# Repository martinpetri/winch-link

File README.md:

# winch-link

This is a new project and intended to facilitate communication when launching a paraglider with a winch, as the usual communication via radio often causes problems.

This requires one device for the launch leader and one for the winch.
"winch link" is to transmit the different states like "pilot ready to launch", "pilot hooked in", "tighten rope" etc. to the winch by pressing a button. The winch operator can set his device to confirm automatically or by pressing a button.

Currently the device is under development (See [hardware/winch-link](hardware/winch-link)). The circuit board is drawn and the first prototypes will be ordered in the next weeks. The device will be equipped with an e-paper display so that it can be read in direct sunlight. 

## MIT License

Copyright (c) [2023] [Martin Petri]

Permission is hereby granted, free of charge, to any person obtaining a copy
of this software and associated documentation files (the "Software"), to deal
in the Software without restriction, including without limitation the rights
to use, copy, modify, merge, publish, distribute, sublicense, and/or sell
copies of the Software, and to permit persons to whom the Software is
furnished to do so, subject to the following conditions:

The above copyright notice and this permission notice shall be included in all
copies or substantial portions of the Software.

THE SOFTWARE IS PROVIDED "AS IS", WITHOUT WARRANTY OF ANY KIND, EXPRESS OR
IMPLIED, INCLUDING BUT NOT LIMITED TO THE WARRANTIES OF MERCHANTABILITY,
FITNESS FOR A PARTICULAR PURPOSE AND NONINFRINGEMENT. IN NO EVENT SHALL THE
AUTHORS OR COPYRIGHT HOLDERS BE LIABLE FOR ANY CLAIM, DAMAGES OR OTHER
LIABILITY, WHETHER IN AN ACTION OF CONTRACT, TORT OR OTHERWISE, ARISING FROM,
OUT OF OR IN CONNECTION WITH THE SOFTWARE OR THE USE OR OTHER DEALINGS IN THE
SOFTWARE.

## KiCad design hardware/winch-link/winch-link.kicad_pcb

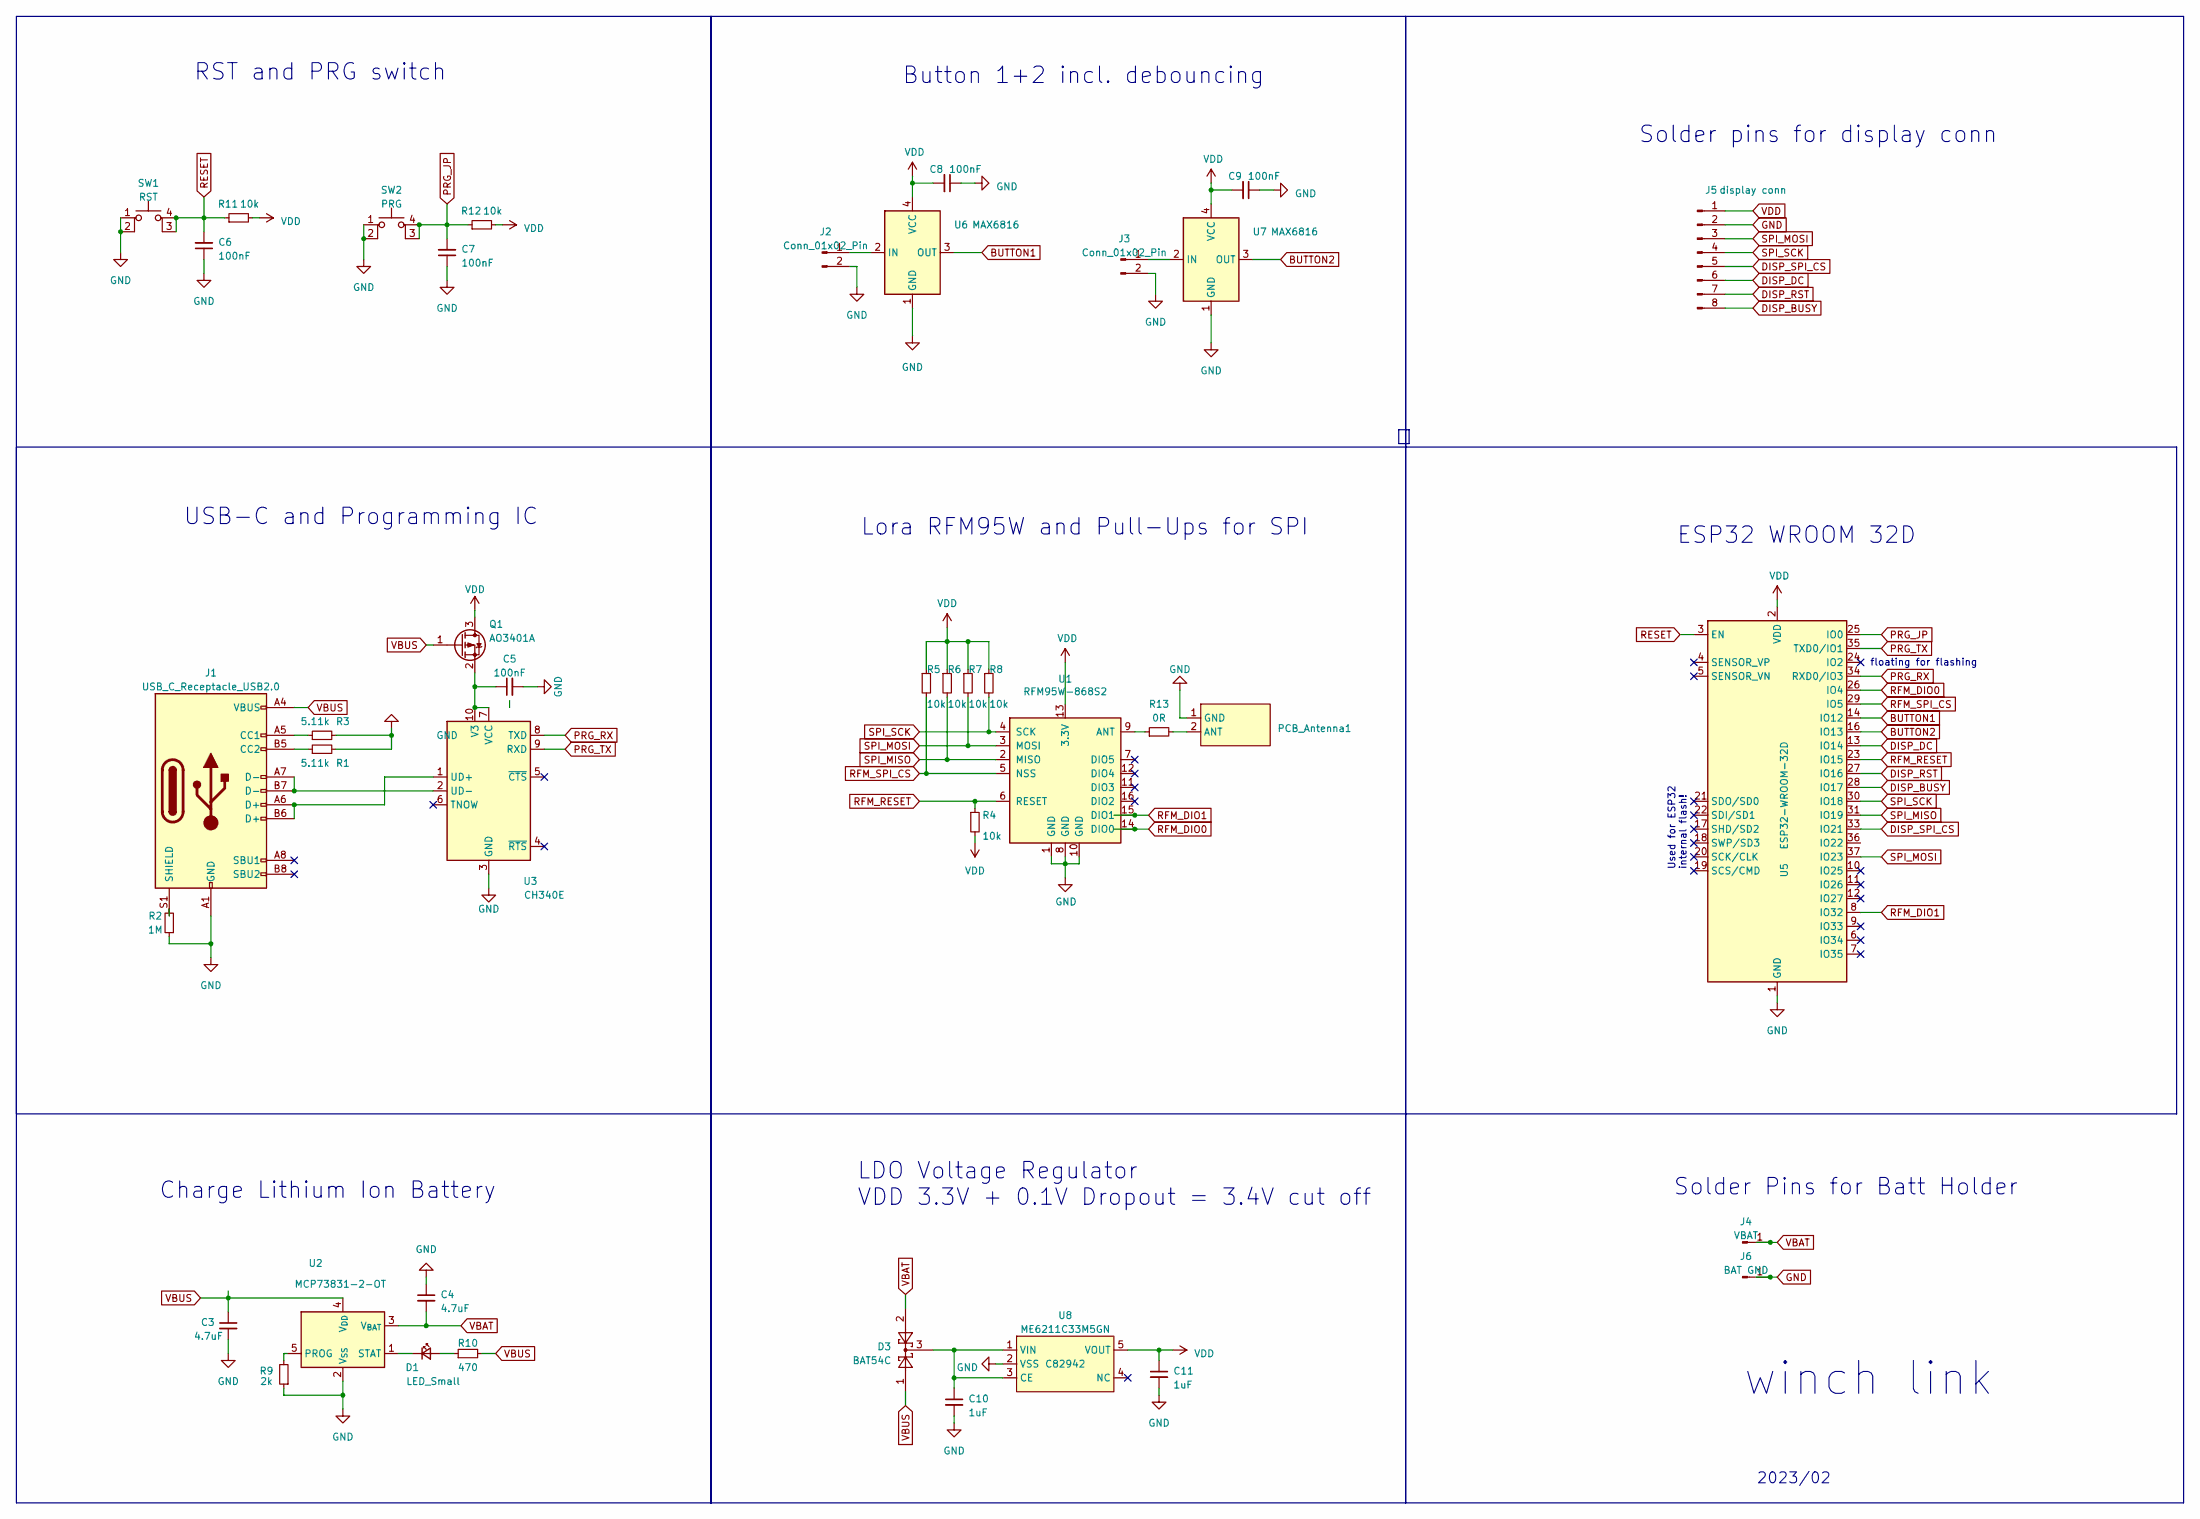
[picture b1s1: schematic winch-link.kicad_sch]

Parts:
C3, C4: 4.7uF; R_0402_1005Metric; LCSC C87147
C5, C6, C7, C8, C9: 100nF; R_0402_1005Metric; LCSC C338032
C10, C11: 1uF; R_0402_1005Metric; LCSC C325464
D1: LED_Small; LED_0603_1608Metric; LCSC C2286
D3: BAT54C; SOT-23; LCSC C171429
J1: USB_C_Receptacle_USB2.0; USB_C_Receptacle_HRO_TYPE-C-31-M-12; LCSC C167321
J2, J3: Conn_01x02_Pin; PinSocket_1x02_P2.54mm_Vertical
J4: VBAT; PinHeader_1x01_P2.54mm_Vertical
J5: display conn; PinHeader_1x08_P2.54mm_Vertical
J6: BAT GND; PinHeader_1x01_P2.54mm_Vertical
PCB_Antenna1: pcb antenna
Q1: AO3401A; SOT-23; LCSC AO3401A
R1, R3: 5.11k; R_0402_1005Metric; LCSC C103084
R2: 1M; R_0402_1005Metric; LCSC C269676
R4, R5, R6, R7, R8, R11, R12: 10k; R_0402_1005Metric; LCSC C406733
R9: 2k; R_0402_1005Metric; LCSC C409711
R10: 470; R_0402_1005Metric; LCSC C114877
R13: 0R; R_0603_1608Metric; LCSC C21189
SW1: RST; SW_TS-1187A-B-A-B; LCSC C318889
SW2: PRG; SW_TS-1187A-B-A-B; LCSC C318889
U1: RFM95W-868S2; HOPERF_RFM9XW_SMD; LCSC C2844472
U2: MCP73831-2-OT; SOT-23-5; LCSC C424093
U3: CH340E; MSOP-10_3x3mm_P0.5mm; LCSC C99652
U5: ESP32-WROOM-32D; LCSC C473012
U6, U7: MAX6816; SOT-143; LCSC C41637
U8: ME6211C33M5GN; SOT-23-5; LCSC C82942

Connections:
BUTTON1: U5.14 (IO12), U6.3 (OUT)
BUTTON2: U5.16 (IO13), U7.3 (OUT)
DISP_BUSY: J5.8, U5.28 (IO17)
DISP_DC: J5.6, U5.13 (IO14)
DISP_RST: J5.7, U5.27 (IO16)
DISP_SPI_CS: J5.5, U5.33 (IO21)
GND: C3.2, C4.1, C5.2, C6.1, C7.1, C8.1, C9.1, C10.2, C11.2, J1.A1 (GND), J1.A12 (GND), J1.B1 (GND), J1.B12 (GND), J2.2, J3.2, J5.2, J6.1, PCB_Antenna1.1 (GND), R1.2, R2.1, R3.2, R9.1, SW1.1, SW1.2, SW2.1, SW2.2, U1.1 (GND), U1.8 (GND), U1.10 (GND), U2.2 (V_{SS}), U3.3 (GND), U5.1 (GND), U5.15 (GND), U5.38 (GND), U5.39 (GND), U6.1 (GND), U7.1 (GND), U8.2 (VSS)
unnamed: D1.2 (A), R10.1
unnamed: D1.1 (K), U2.1 (STAT)
unnamed: J1.A5 (CC1), R3.1
unnamed: J1.B5 (CC2), R1.1
unnamed: J1.S1 (SHIELD), R2.2
unnamed: J2.1, U6.2 (IN)
unnamed: J3.1, U7.2 (IN)
unnamed: PCB_Antenna1.2 (ANT), R13.2
unnamed: C5.1, Q1.2 (S), U3.7 (VCC), U3.10 (V3)
unnamed: R13.1, U1.9 (ANT)
unnamed: R9.2, U2.5 (PROG)
unnamed: J1.A6 (D+), J1.B6 (D+), U3.1 (UD+)
unnamed: J1.A7 (D-), J1.B7 (D-), U3.2 (UD-)
unnamed: C10.1, D3.3, U8.1 (VIN), U8.3 (CE)
PRG_JP: C7.2, R12.1, SW2.3 (K), SW2.4 (A), U5.25 (IO0)
PRG_RX: U3.8 (TXD), U5.34 (RXD0/IO3)
PRG_TX: U3.9 (RXD), U5.35 (TXD0/IO1)
RESET: C6.2, R11.1, SW1.3, SW1.4, U5.3 (EN)
RFM_DIO0: U1.14 (DIO0), U5.26 (IO4)
RFM_DIO1: U1.15 (DIO1), U5.8 (IO32)
RFM_RESET: R4.1, U1.6 (RESET), U5.23 (IO15)
RFM_SPI_CS: R5.2, U1.5 (NSS), U5.29 (IO5)
SPI_MISO: R6.2, U1.2 (MISO), U5.31 (IO19)
SPI_MOSI: J5.3, R7.2, U1.3 (MOSI), U5.37 (IO23)
SPI_SCK: J5.4, R8.2, U1.4 (SCK), U5.30 (IO18)
VBAT: C4.2, D3.2, J4.1, U2.3 (V_{BAT})
VBUS: C3.1, D3.1, J1.A4 (VBUS), J1.A9 (VBUS), J1.B4 (VBUS), J1.B9 (VBUS), Q1.1 (G), R10.2, U2.4 (V_{DD})
VDD: C8.2, C9.2, C11.1, J5.1, Q1.3 (D), R4.2, R5.1, R6.1, R7.1, R8.1, R11.2, R12.2, U1.13 (3.3V), U5.2 (VDD), U6.4 (VCC), U7.4 (VCC), U8.5 (VOUT)

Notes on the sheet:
Lora RFM95W and Pull-Ups for SPI
2023/02
Charge Lithium Ion Battery
floating for flashing
Used for ESP32 internal flash!
Solder Pins for Batt Holder
RST and PRG switch
Solder pins for display conn
LDO Voltage Regulator VDD 3.3V + 0.1V Dropout = 3.4V cut off
ESP32 WROOM 32D
USB-C and Programming IC
Button 1+2 incl. debouncing
winch link

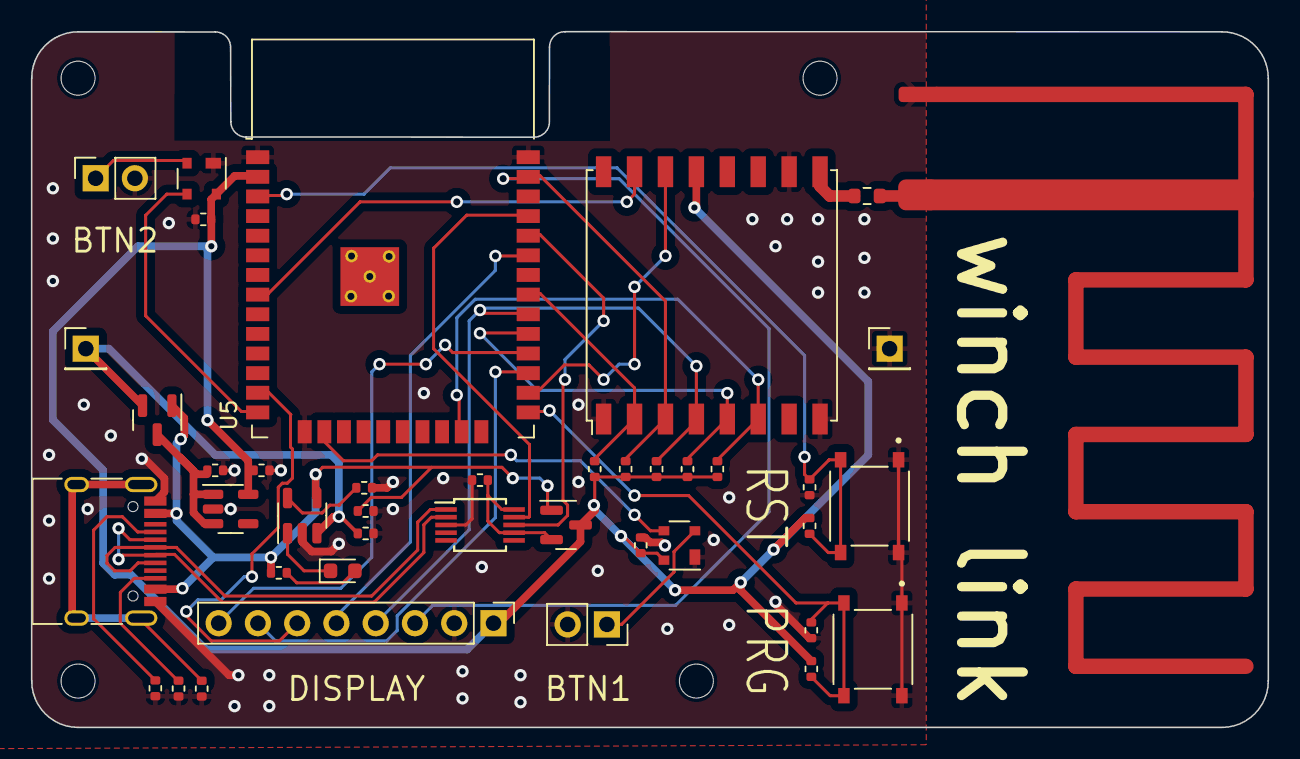
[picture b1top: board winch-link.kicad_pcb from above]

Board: 2 copper layers, 80.0 x 45.0 mm, 41 parts (0 on the bottom side), 35 nets.

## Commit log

2023-02-28 first commit hardware
2023-03-01 Add BOM and CPL files
2023-03-01 Add README.md
2023-03-01 Minor corrections
2023-03-01 Add schematic.pdf
